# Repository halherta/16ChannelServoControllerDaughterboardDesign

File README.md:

# 16ChannelServoControllerDaughterboardDesign
16 Channel Servo (&amp; PWM) Controller Daughterboard Design using a PCA9685. Part of the IOT innovation station project

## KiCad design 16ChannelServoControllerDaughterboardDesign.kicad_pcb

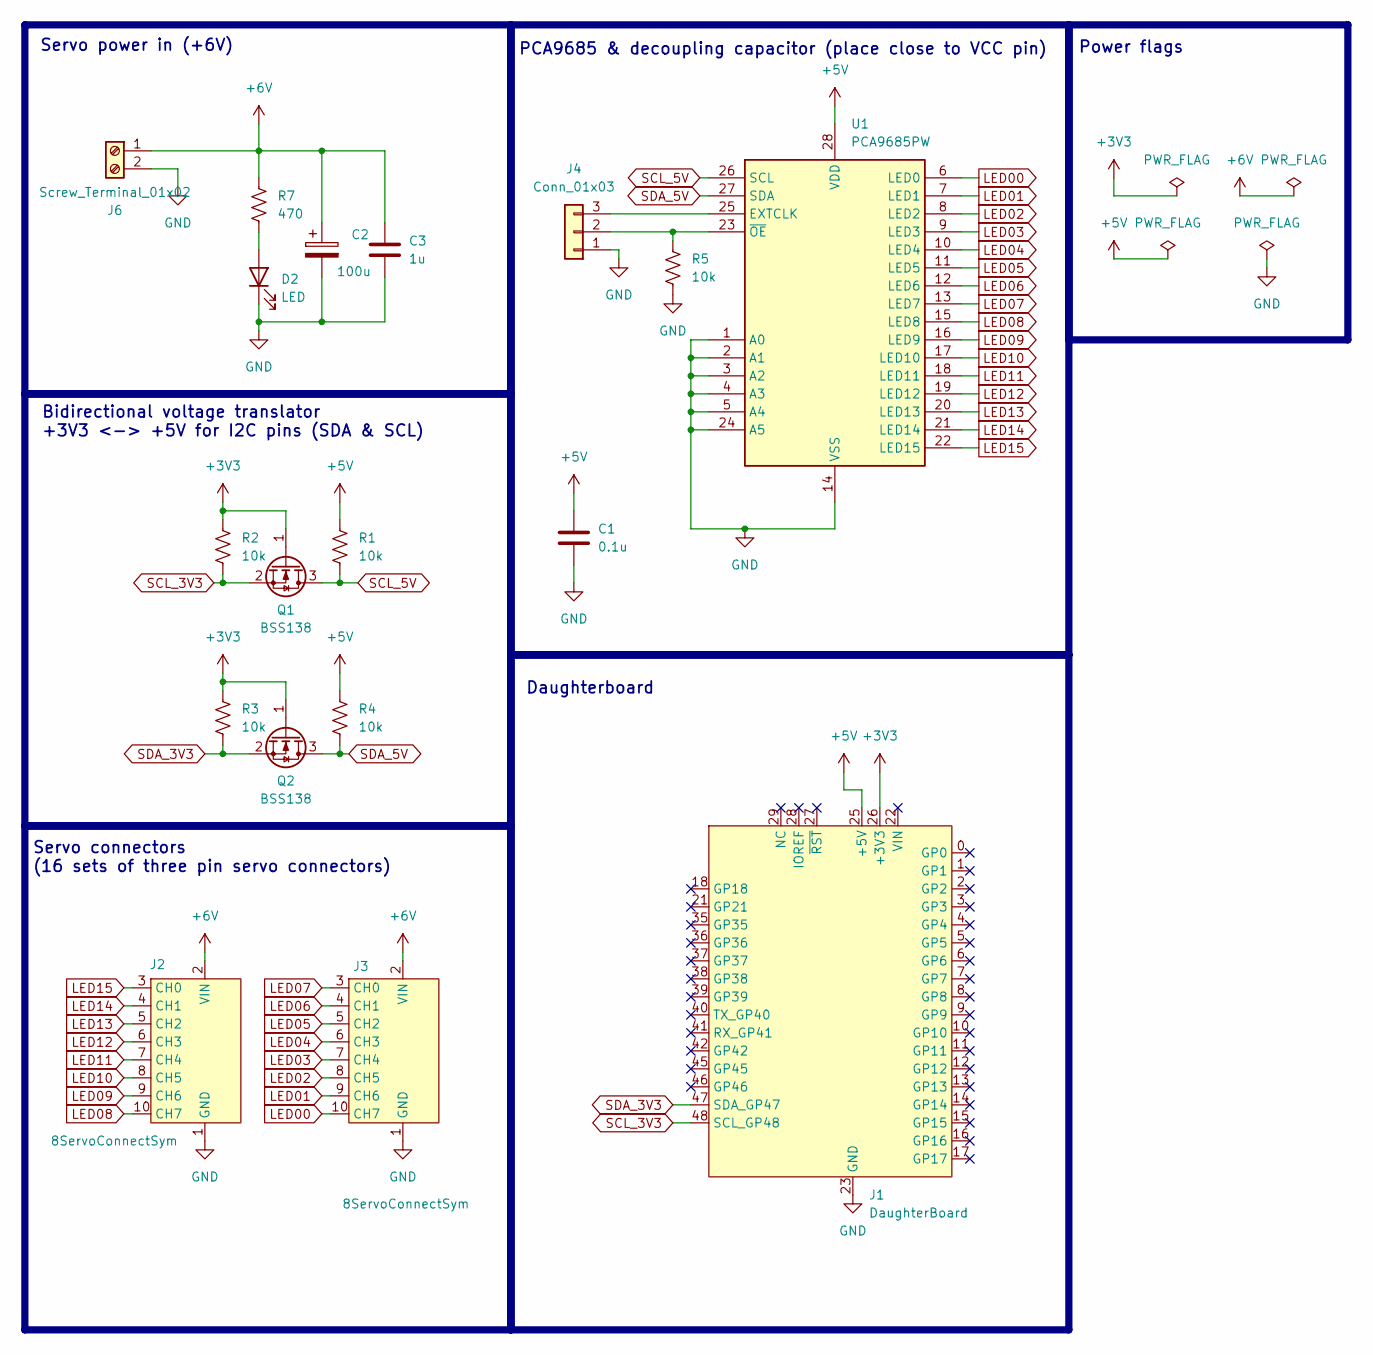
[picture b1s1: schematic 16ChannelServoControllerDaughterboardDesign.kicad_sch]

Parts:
C1: 0.1u; C_1206_3216Metric_Pad1.33x1.80mm_HandSolder
C2: 100u; CP_Elec_6.3x7.7
C3: 1u; C_1206_3216Metric_Pad1.33x1.80mm_HandSolder
D2: LED; LED_1206_3216Metric_Pad1.42x1.75mm_HandSolder
J1: DaughterBoard; DaughterBoardTemplate
J2, J3: 8ServoConnectSym; 8ServoConnect
J4: Conn_01x03; PinHeader_1x03_P2.54mm_Vertical
J6: Screw_Terminal_01x02; TerminalBlock_Phoenix_MKDS-1,5-2_1x02_P5.00mm_Horizontal
Q1, Q2: BSS138; SOT-23
R1, R2, R3, R4, R5: 10k; R_1206_3216Metric_Pad1.30x1.75mm_HandSolder
R7: 470; R_1206_3216Metric_Pad1.30x1.75mm_HandSolder
U1: PCA9685PW; TSSOP-28_4.4x9.7mm_P0.65mm

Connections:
+3V3: J1.26 (+3V3), J1.32 (+3V3), Q1.1 (G), Q2.1 (G), R2.1, R3.1
+5V: C1.1, J1.25 (+5V), R1.1, R4.1, U1.28 (VDD)
+6V: C2.1, C3.1, J2.2 (VIN), J3.2 (VIN), J6.1, R7.1
GND: C1.2, C2.2, C3.2, D2.1 (K), J1.23 (GND), J1.24 (GND), J1.30 (GND), J2.1 (GND), J3.1 (GND), J4.1, J6.2, R5.2, U1.1 (A0), U1.2 (A1), U1.3 (A2), U1.4 (A3), U1.5 (A4), U1.14 (VSS), U1.24 (A5)
LED00: J3.10 (CH7), U1.6 (LED0)
LED01: J3.9 (CH6), U1.7 (LED1)
LED02: J3.8 (CH5), U1.8 (LED2)
LED03: J3.7 (CH4), U1.9 (LED3)
LED04: J3.6 (CH3), U1.10 (LED4)
LED05: J3.5 (CH2), U1.11 (LED5)
LED06: J3.4 (CH1), U1.12 (LED6)
LED07: J3.3 (CH0), U1.13 (LED7)
LED08: J2.10 (CH7), U1.15 (LED8)
LED09: J2.9 (CH6), U1.16 (LED9)
LED10: J2.8 (CH5), U1.17 (LED10)
LED11: J2.7 (CH4), U1.18 (LED11)
LED12: J2.6 (CH3), U1.19 (LED12)
LED13: J2.5 (CH2), U1.20 (LED13)
LED14: J2.4 (CH1), U1.21 (LED14)
LED15: J2.3 (CH0), U1.22 (LED15)
unnamed: D2.2 (A), R7.2
unnamed: J4.2, R5.1, U1.23 (~OE)
unnamed: J4.3, U1.25 (EXTCLK)
SCL_3V3: J1.48 (SCL_GP48), Q1.2 (S), R2.2
SCL_5V: Q1.3 (D), R1.2, U1.26 (SCL)
SDA_3V3: J1.47 (SDA_GP47), Q2.2 (S), R3.2
SDA_5V: Q2.3 (D), R4.2, U1.27 (SDA)

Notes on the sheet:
Bidirectional voltage translator +3V3 <-> +5V for I2C pins (SDA & SCL)
Servo connectors (16 sets of three pin servo connectors)
Daughterboard
Power flags
Servo power in (+6V)
PCA9685 & decoupling capacitor (place close to VCC pin)

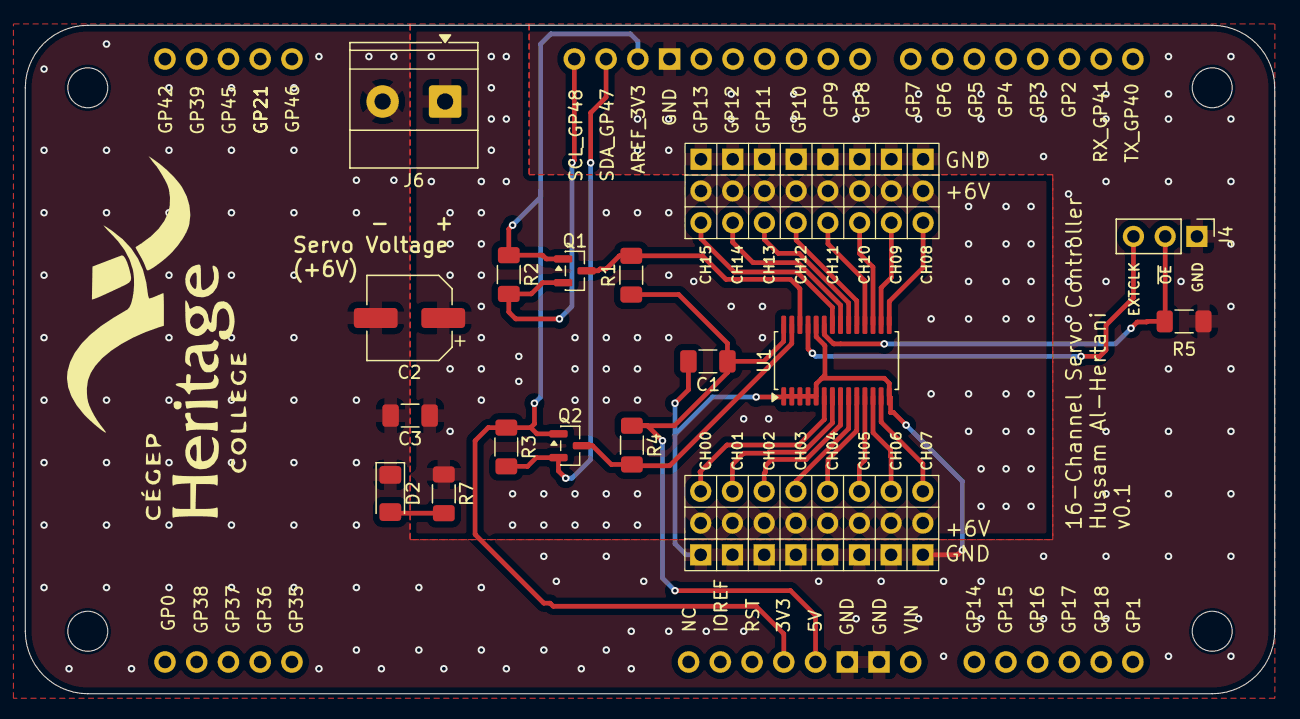
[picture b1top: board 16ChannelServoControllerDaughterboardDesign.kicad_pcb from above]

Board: 2 copper layers, 100.0 x 53.5 mm, 18 parts (0 on the bottom side), 27 nets.

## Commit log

2024-11-01 added Readme
2025-09-30 updated some things
